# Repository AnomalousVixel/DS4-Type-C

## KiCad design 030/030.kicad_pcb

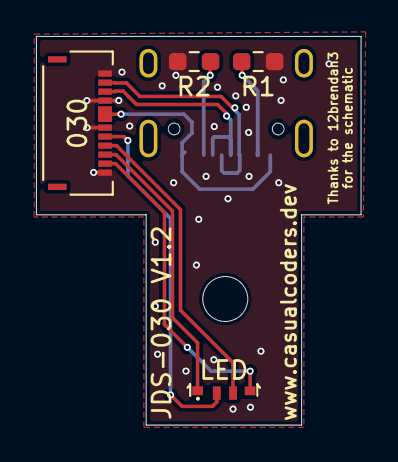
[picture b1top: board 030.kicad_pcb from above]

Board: 2 copper layers, 18.0 x 21.6 mm, 5 parts (1 on the bottom side), 10 nets.

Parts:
J1: 030; 503480-1200
LED: LED_RAGB; FM-3510RGBA-SG
R1, R2: 5.1k; R_0603_1608Metric_Pad0.98x0.95mm_HandSolder
USB: USB_C_Receptacle_USB2.0; USB_C_Receptacle_HRO_TYPE-C-31-M-12

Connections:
+5V: J1.5, J1.6, USB.A4 (VBUS), USB.A9 (VBUS), USB.B4 (VBUS), USB.B9 (VBUS)
/Annode: J1.8, LED.2 (A)
/B: J1.11, LED.4 (BK)
/D+: J1.2, USB.A6 (D+), USB.B6 (D+)
/D-: J1.3, USB.A7 (D-), USB.B7 (D-)
/G: J1.9, LED.3 (GK)
/R: J1.10, LED.1 (RK)
GND: J1.1, J1.4, J1.7, J1.12, R1.2, R2.1, USB.A1 (GND), USB.A12 (GND), USB.B1 (GND), USB.B12 (GND)
unnamed: R1.1, USB.B5 (CC2)
unnamed: R2.2, USB.A5 (CC1)

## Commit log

2024-01-09 Updated 030 files and thumbnails

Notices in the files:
parts and their libraries:
Copyright 2021 Accelerated Designs. All rights reserved.
